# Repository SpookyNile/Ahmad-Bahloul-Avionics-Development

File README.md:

# Ahmad Bahloul Avionics Development (ABAD)

## Objective
Brainstorm, design, construct and revise a flight computer for high power rocket avionics.

## Requirements (from high-low priority)
- Capable of Dual Deploy, detect launch, flight, apogee, and fire respective pyrotechnics for drogue and main parachute at programmable altitudes.
- Detect and record max altitude, speed, and acceleration
- GPS/GNSS Location tracker to aid in recovery, preferably with Live telemetry
- High-speed data logging to onboard non-volatile flash memory and SD card
- Live Telemetry to ground during flight over 915 or 433 MHz with Live Ground station UI
- Redundancy and safety checks of the board and its systems to prevent accidental burnouts, shorts, and accidents upon startup and pre-flight
- Ability to fire parachutes early or not fire parachutes at all if flight profile is irregular or not met.
- Use data to have velocity and position predictions accurately

## Hardware
**MCU**: ESP32-S3-WROOM-1
**MPU**: MPU6050  
**LoRa**: REYAX RYLR998  
**GPS**: Beitian Dual BN-220  
**Pressure & Temperature Sensor**: MS5611

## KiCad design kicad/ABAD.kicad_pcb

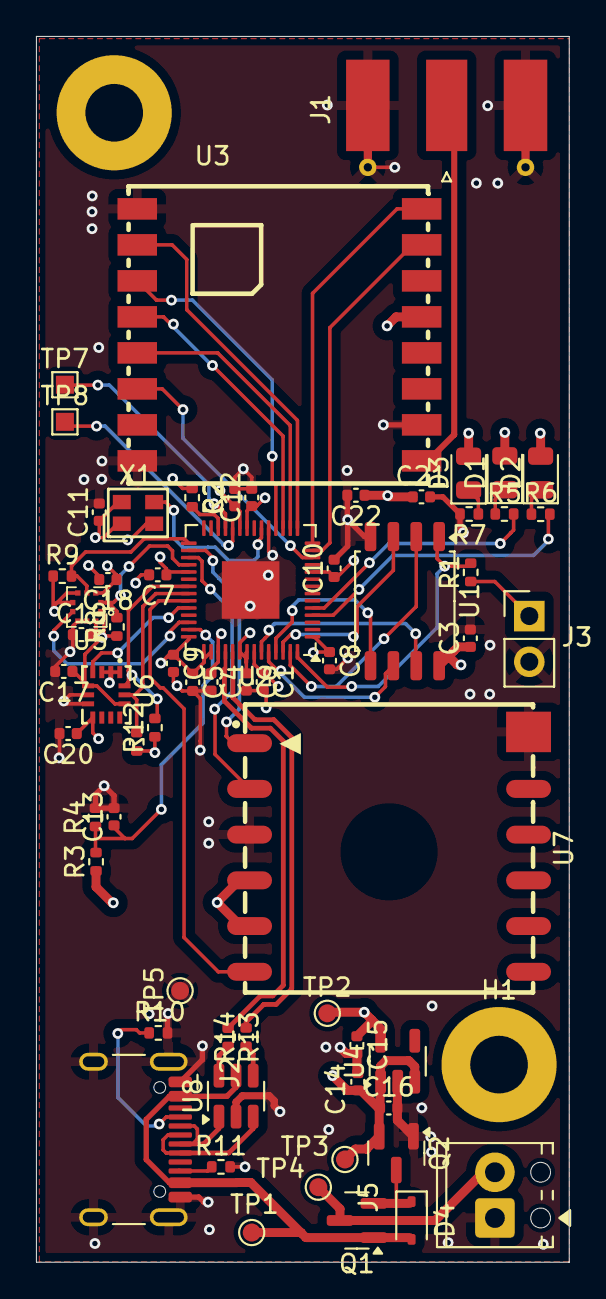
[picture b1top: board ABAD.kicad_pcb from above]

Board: 4 copper layers, 29.6 x 68.1 mm, 65 parts (0 on the bottom side), 49 nets.

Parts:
C1, C2, C3, C6, C7, C8, C9, C10, C11, C12, C13, C17, C18, C19, C20, C21: 100nF; C_0402_1005Metric
C4, C5, C14, C15: 1uF; C_0402_1005Metric
C16, C22: 10uF; C_0402_1005Metric
D1: RF_LED_GREEN; LED_0805_2012Metric
D2: GPS_LED_BLUE; LED_0805_2012Metric
D3: PWR_LED_RED; LED_0805_2012Metric
D4: D_Schottky; D_SOD-323
H1, H2: MountingHole; MountingHole_3.2mm_M3_Pad
J1: Edge mounted SMA; SMA_Molex_73251-1153_EdgeMount_Horizontal
J2: USB_C_Receptacle_USB2.0_16P; USB_C_Receptacle_HCTL_HC-TYPE-C-16P-01A
J3: Conn_01x02; PinHeader_1x02_P2.54mm_Vertical
J5: BATT Screw Terminal; TerminalBlock_Phoenix_MPT-0,5-2-2.54_1x02_P2.54mm_Horizontal
Q1, Q2: AO3401A; SOT-23
R1, R5, R6, R7: 1k; R_0402_1005Metric
R2, R10, R11: 5.1k; R_0402_1005Metric
R3: 30k; R_0402_1005Metric
R4: 51k; R_0402_1005Metric
R8, R9: 4.7k; R_0402_1005Metric
R12, R15: 10k; R_0402_1005Metric
R13, R14: 22Ω; R_0402_1005Metric
TP1: VBUS; TestPoint_Pad_D1.0mm
TP2: 3.3V; TestPoint_Pad_D1.0mm
TP3: BATT+; TestPoint_Pad_D1.0mm
TP4: BATT_RAW+; TestPoint_Pad_D1.0mm
TP5: GND; TestPoint_Pad_D1.0mm
TP7: SWCLK; TestPoint_Pad_1.0x1.0mm
TP8: SWD; TestPoint_Pad_1.0x1.0mm
U1: W25Q128JVS; SOIC-8_5.3x5.3mm_P1.27mm
U2: RP2040; QFN-56-1EP_7x7mm_P0.4mm_EP3.2x3.2mm
U3: 433MHz; LCC-16_L16.0-W16.0-P2.00-TL
U4: AP2112K-3.3; SOT-23-5
U5: BMP390; LGA-10_L2.0-W2.0-P0.50-TL_BMP390L
U6: LSMDSO32TR; LGA-14_L3.0-W2.5-P0.50-TL
U7: L80RE-M37; GPSM-SMD_12P-L16.0-W16.0-P2.54-BL
U8: USBLC6-2SC6; SOT-23-6
X1: 12MHz; OSC-SMD_4P-L2.0-W1.6-BL

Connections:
+1V1: C1.1, C2.1, C4.1, U2.23 (DVDD), U2.45 (VREG_VOUT), U2.50 (DVDD)
+3V3: C3.1, C5.1, C6.1, C7.1, C8.1, C9.1, C10.1, C11.1, C12.1, C15.1, C17.1, C18.2, C19.2, C20.1, C21.1, C22.1, D1.2 (A), D2.2 (A), D3.2 (A), R2.1, R8.1, R9.1, R12.1, R15.1, TP2.1, U1.8 (VCC), U2.1 (IOVDD), U2.10 (IOVDD), U2.22 (IOVDD), U2.33 (IOVDD), U2.42 (IOVDD), U2.43 (ADC_AVDD), U2.44 (VREG_IN), U2.48 (USB_VDD), U2.49 (IOVDD), U3.13 (VCC), U4.5 (VOUT), U5.1 (VDDIO), U5.5 (SDO), U5.6 (CSB), U5.10 (VDD), U6.5 (VDDIO), U6.8 (VDD), U6.12 (CS), U7.4 (VCC), U7.5 (V_BCKP), X1.1 (OE/NC), X1.4 (VDD)
+BATT: C14.1, C16.1, Q2.2 (S), R3.1, TP3.1, U4.1 (VIN), U4.3 (EN)
/ACCEL_INT: U2.38 (GPIO26_ADC0), U6.4 (INT1)
/ACCEL_SCL: R15.2, U2.36 (GPIO24), U6.13 (SCL)
/ACCEL_SDA: R12.2, U2.35 (GPIO23), U6.14 (SDA)
/BATT SENSE: C13.1, R3.2, R4.1, U2.41 (GPIO29_ADC3)
/BMP_INT: U2.40 (GPIO28_ADC2), U5.7 (INT)
/BMP_SCL: R8.2, U2.32 (GPIO21), U5.2 (SCK)
/BMP_SDA: R9.2, U2.29 (GPIO18), U5.4 (SDI)
/BOOTSEL: J3.1, R1.1
/BUSY: U2.14 (GPIO11), U3.16 (BUSY)
/DIO1: U2.13 (GPIO10), U3.15 (DIO1)
/GPS_RX: U2.30 (GPIO19), U7.1 (RXD1)
/GPS_TX: U2.31 (GPIO20), U7.2 (TXD1)
/MISO: U2.15 (GPIO12), U3.2 (MISO)
/MOSI: U2.18 (GPIO15), U3.3 (MOSI)
/NSS: U2.16 (GPIO13), U3.5 (NSS)
/PPS: U2.37 (GPIO25), U7.6 (1PPS)
/PPS_LED: R6.2, U2.4 (GPIO2)
/QSPI_SCLK: U1.6 (CLK), U2.52 (QSPI_SCLK)
/QSPI_SD0: U1.5 (DI/IO_{0}), U2.53 (QSPI_SD0)
/QSPI_SD1: U1.2 (DO/IO_{1}), U2.55 (QSPI_SD1)
/QSPI_SD2: U1.3 (~WP/IO_{2}), U2.54 (QSPI_SD2)
/QSPI_SD3: U1.7 (~HOLD/~RESET/IO_{3}), U2.51 (QSPI_SD3)
/QSPI_SS: R1.2, U1.1 (~CS), U2.56 (QSPI_SS)
/RESET: U2.12 (GPIO9), U3.6 (NRESET)
/RF_LED: R5.2, U2.5 (GPIO3)
/RUN: R2.2, U2.26 (RUN)
/SCK: U2.17 (GPIO14), U3.4 (SCK)
/SWCLK: TP8.1, U2.24 (SWCLK)
/SWD: TP7.1, U2.25 (SWD)
/USB_D+: R14.2, U2.47 (USB_DP)
/USB_D-: R13.1, U2.46 (USB_DM)
/XIN: U2.20 (XIN), X1.3 (OUT)
GND: C1.2, C2.2, C3.2, C4.2, C5.2, C6.2, C7.2, C8.2, C9.2, C10.2, C11.2, C12.2, C13.2, C14.2, C15.2, C16.2, C17.2, C18.1, C19.1, C20.2, C21.2, C22.2, J1.2 (Ext), J2.A1 (GND), J2.A12 (GND), J2.B1 (GND), J2.B12 (GND), J2.S1 (SHIELD), J3.2, J5.1, Q2.1 (G), R4.2, R7.2, R10.2, R11.2, TP5.1, U1.4 (GND), U2.19 (TESTEN), U2.57 (GND), U3.1 (GND), U3.8 (GND), U3.10 (GND), U4.2 (GND), U5.3 (VSS), U5.8 (VSS), U5.9 (VSS), U6.1 (SDO/SA0), U6.2 (SDx), U6.3 (SCx), U6.6 (GND), U6.7 (GND), U7.3 (GND), U7.12 (GND), U8.2 (GND), X1.2 (GND)
unnamed: D1.1 (K), R5.1
unnamed: D2.1 (K), R6.1
unnamed: D3.1 (K), R7.1
unnamed: D4.1 (K), Q1.2 (S), Q2.3 (D)
unnamed: J1.1 (In), U3.9 (ANT)
unnamed: J2.A5 (CC1), R10.1
unnamed: J2.B5 (CC2), R11.1
unnamed: J2.A6 (D+), J2.B6 (D+), U8.3 (I/O2)
unnamed: J2.A7 (D-), J2.B7 (D-), U8.1 (I/O1)
unnamed: R13.2, U8.6 (I/O1)
unnamed: R14.1, U8.4 (I/O2)
RAW_BATT+: J5.2, Q1.3 (D), TP4.1
VBUS: D4.2 (A), J2.A4 (VBUS), J2.A9 (VBUS), J2.B4 (VBUS), J2.B9 (VBUS), Q1.1 (G), TP1.1, U8.5 (VBUS)

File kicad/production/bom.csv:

Designator,Footprint,Quantity,Value,LCSC Part #
"C1, C10, C11, C12, C13, C17, C18, C19, C2, C20, C21, C3, C6, C7, C8, C9",0402,16,100nF,
"C14, C15, C4, C5",0402,4,1uF,
"C16, C22",0402,2,10uF,
D1,0805,1,RF_LED_GREEN,
D2,0805,1,GPS_LED_BLUE,
D3,0805,1,PWR_LED_RED,
D4,D_SOD-323,1,D_Schottky,
J1,SMA_Molex_73251-1153_EdgeMount_Horizontal,1,Edge mounted SMA,
J2,USB_C_Receptacle_HCTL_HC-TYPE-C-16P-01A,1,USB_C_Receptacle_USB2.0_16P,
J3,PinHeader_1x02_P2.54mm_Vertical,1,Conn_01x02,
J5,"TerminalBlock_Phoenix_MPT-0,5-2-2.54_1x02_P2.54mm_Horizontal",1,BATT Screw Terminal,
"Q1, Q2",SOT-23,2,AO3401A,
"R1, R5, R6, R7",0402,4,1k,
"R10, R11, R2",0402,3,5.1k,
"R12, R15",0402,2,10k,
"R13, R14",0402,2,22Ω,
R3,0402,1,30k,
R4,0402,1,51k,
"R8, R9",0402,2,4.7k,
TP1,TestPoint_Pad_D1.0mm,1,VBUS,
TP2,TestPoint_Pad_D1.0mm,1,3.3V,
TP3,TestPoint_Pad_D1.0mm,1,BATT+,
TP4,TestPoint_Pad_D1.0mm,1,BATT_RAW+,
TP5,TestPoint_Pad_D1.0mm,1,GND,
TP7,TestPoint_Pad_1.0x1.0mm,1,SWCLK,
TP8,TestPoint_Pad_1.0x1.0mm,1,SWD,
U1,SOIC-8_5.3x5.3mm_P1.27mm,1,W25Q128JVS,
U2,QFN-56-1EP_7x7mm_P0.4mm_EP3.2x3.2mm,1,RP2040,
U3,LCC-16_L16.0-W16.0-P2.00-TL,1,433MHz,
U4,SOT-23-5,1,AP2112K-3.3,
U5,LGA-10_L2.0-W2.0-P0.50-TL_BMP390L,1,BMP390,
U6,LGA-14_L3.0-W2.5-P0.50-TL,1,LSMDSO32TR,
U7,GPSM-SMD_12P-L16.0-W16.0-P2.54-BL,1,L80RE-M37,
U8,SOT-23-6,1,USBLC6-2SC6,
X1,OSC-SMD_4P-L2.0-W1.6-BL,1,12MHz,

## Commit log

2024-07-14 FirstCommit
2024-09-16 test commit
2024-09-16 HuH?
2024-09-16 Stuff
2024-09-16 youssef
2024-09-16 Kicad added
2025-05-04 Created ESP IDF project
2025-05-04 Added readme
2025-05-23 GPS functionality achieved
2025-05-23 MPU functionality achieved
2025-05-23 Modularized code
2025-05-24 Barometer functionality achieved
2025-06-06 Youssef branch
2025-06-06 Started lora files
2025-06-06 gitignore
2025-06-30 Schematic updated; pcb started; near completion
2025-06-30 Completed first iteration of fc pcb
2025-07-02 Gerber and other output files
2025-07-13 Schematic_Jul12_Nile
2025-07-13 schematic_Jul13_Nile
2025-07-13 schematic July 13 Nile
2025-07-13 rm rf lock file
2025-07-13 Testing branch pulling
2025-07-14 ESD array and Net labels fixed
2025-09-01 4 layer PCB design - now deprecated due to high production cost
2025-09-22 Completed PCB + Sch, RP2040 based
